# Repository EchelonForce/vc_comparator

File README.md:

# Eurorack Comparator Module

This is a design for a eurorack comparator module using an LM393.

Full writeup here: https://www.robotdialogs.com/2023/01/eurorack-comparator-module.html

This work is licensed under a Creative Commons Attribution-NonCommercial-ShareAlike 4.0 International License. https://creativecommons.org/licenses/by-nc-sa/4.0/

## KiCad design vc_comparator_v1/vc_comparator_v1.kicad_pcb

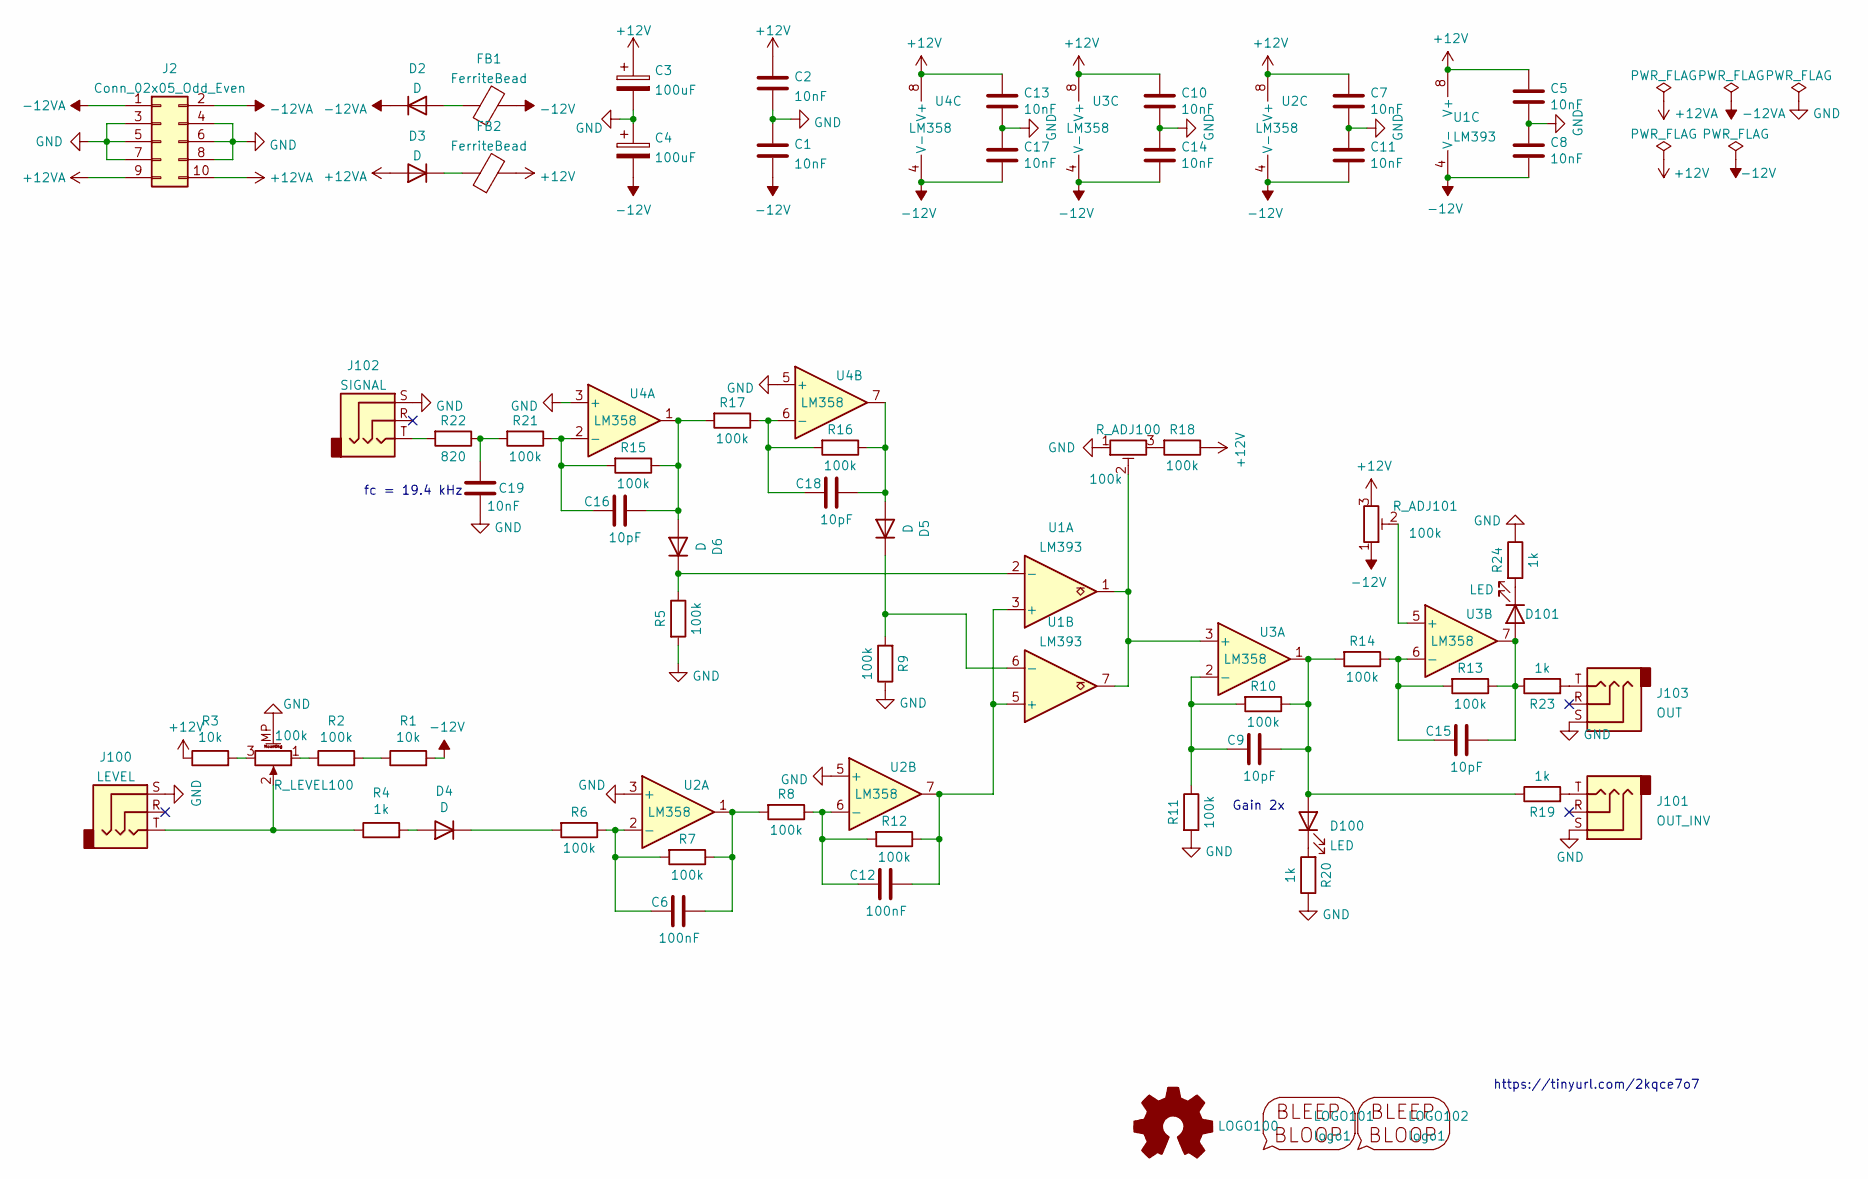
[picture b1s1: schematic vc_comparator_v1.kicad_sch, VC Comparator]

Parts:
C1, C2, C5, C7, C8, C10, C11, C13, C14, C17, C19: 10nF; C_1206_3216Metric_Pad1.33x1.80mm_HandSolder
C3, C4: 100uF; CP_Radial_D5.0mm_P2.50mm
C6, C12: 100nF; C_1206_3216Metric_Pad1.33x1.80mm_HandSolder
C9, C15, C16, C18: 10pF; C_1206_3216Metric_Pad1.33x1.80mm_HandSolder
D2, D3, D4, D5, D6: D; D_A-405_P2.54mm_Vertical_KathodeUp
D100, D101: LED; LED_D3.0mm
FB1, FB2: FerriteBead; L_Axial_L6.6mm_D2.7mm_P2.54mm_Vertical_Vishay_IM-2
J2: Conn_02x05_Odd_Even; IDC-Header_2x05_P2.54mm_Vertical
J100: LEVEL; Jack_3.5mm_MJ-355W_Vertical
J101: OUT_INV; Jack_3.5mm_MJ-355W_Vertical
J102: SIGNAL; Jack_3.5mm_MJ-355W_Vertical
J103: OUT; Jack_3.5mm_MJ-355W_Vertical
LOGO100: Logo_Open_Hardware_Small; OSHW-Symbol_6.7x6mm_SilkScreen
LOGO101: logo1; Logo1
LOGO102: logo1; Logo2
R1, R3: 10k; R_1206_3216Metric_Pad1.30x1.75mm_HandSolder
R2, R5, R6, R7, R8, R9, R10, R11, R12, R13, R14, R15, R16, R17, R18, R21: 100k; R_1206_3216Metric_Pad1.30x1.75mm_HandSolder
R4, R19, R20, R23, R24: 1k; R_1206_3216Metric_Pad1.30x1.75mm_HandSolder
R22: 820; R_1206_3216Metric_Pad1.30x1.75mm_HandSolder
R_ADJ100, R_ADJ101: 100k; Potentiometer_Bourns_3296W_Vertical
R_LEVEL100: 100k; Potentiometer_Alpha_RD901F-40-00D_Single_Vertical_w_3d
U1: LM393; DIP-8_W7.62mm_Socket_LongPads
U2, U3, U4: LM358; DIP-8_W7.62mm_Socket_LongPads

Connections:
+12V: C2.1, C3.1, C5.2, C7.2, C10.2, C13.2, FB2.2, R3.1, R18.1, R_ADJ101.3, U1.8 (V+), U2.8 (V+), U3.8 (V+), U4.8 (V+)
+12VA: D3.2 (A), J2.9, J2.10
-12V: C1.2, C4.2, C8.1, C11.1, C14.1, C17.1, FB1.2, R1.2, R_ADJ101.1, U1.4 (V-), U2.4 (V-), U3.4 (V-), U4.4 (V-)
-12VA: D2.1 (K), J2.1, J2.2
GND: C1.1, C2.2, C3.2, C4.1, C5.1, C7.1, C8.2, C10.1, C11.2, C13.1, C14.2, C17.2, C19.2, J2.3, J2.4, J2.5, J2.6, J2.7, J2.8, J100.S, J101.S, J102.S, J103.S, R5.2, R9.1, R11.2, R20.1, R24.1, R_ADJ100.1, R_LEVEL100.MP (MountPin), U2.3 (+), U2.5 (+), U4.3 (+), U4.5 (+)
unnamed: C6.1, R7.1, R8.2, U2.1
unnamed: C6.2, R6.1, R7.2, U2.2 (-)
unnamed: C9.1, D100.2 (A), R10.1, R14.2, R19.1, U3.1
unnamed: C9.2, R10.2, R11.1, U3.2 (-)
unnamed: C12.1, R12.1, U1.3 (+), U1.5 (+), U2.7
unnamed: C12.2, R8.1, R12.2, U2.6 (-)
unnamed: C15.1, D101.2 (A), R13.1, R23.1, U3.7
unnamed: C15.2, R13.2, R14.1, U3.6 (-)
unnamed: C16.1, D6.2 (A), R15.1, R17.2, U4.1
unnamed: C16.2, R15.2, R21.1, U4.2 (-)
unnamed: C18.1, D5.2 (A), R16.1, U4.7
unnamed: C18.2, R16.2, R17.1, U4.6 (-)
unnamed: C19.1, R21.2, R22.1
unnamed: D2.2 (A), FB1.1
unnamed: D3.1 (K), FB2.1
unnamed: D4.1 (K), R6.2
unnamed: D4.2 (A), R4.2
unnamed: D5.1 (K), R9.2, U1.6 (-)
unnamed: D6.1 (K), R5.1, U1.2 (-)
unnamed: D100.1 (K), R20.2
unnamed: D101.1 (K), R24.2
unnamed: J100.T, R4.1, R_LEVEL100.2
unnamed: J101.T, R19.2
unnamed: J102.T, R22.2
unnamed: J103.T, R23.2
unnamed: R2.1, R_LEVEL100.1
unnamed: R1.1, R2.2
unnamed: R3.2, R_LEVEL100.3
unnamed: R18.2, R_ADJ100.3
unnamed: R_ADJ100.2, U1.1, U1.7, U3.3 (+)
unnamed: R_ADJ101.2, U3.5 (+)

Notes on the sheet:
fc = 19.4 kHz
Gain 2x
https://tinyurl.com/2kqce7o7

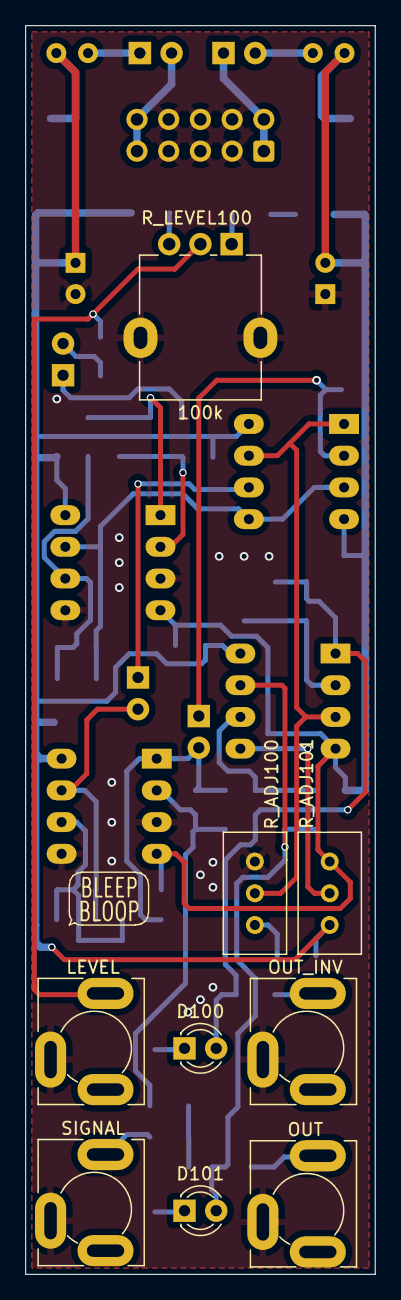
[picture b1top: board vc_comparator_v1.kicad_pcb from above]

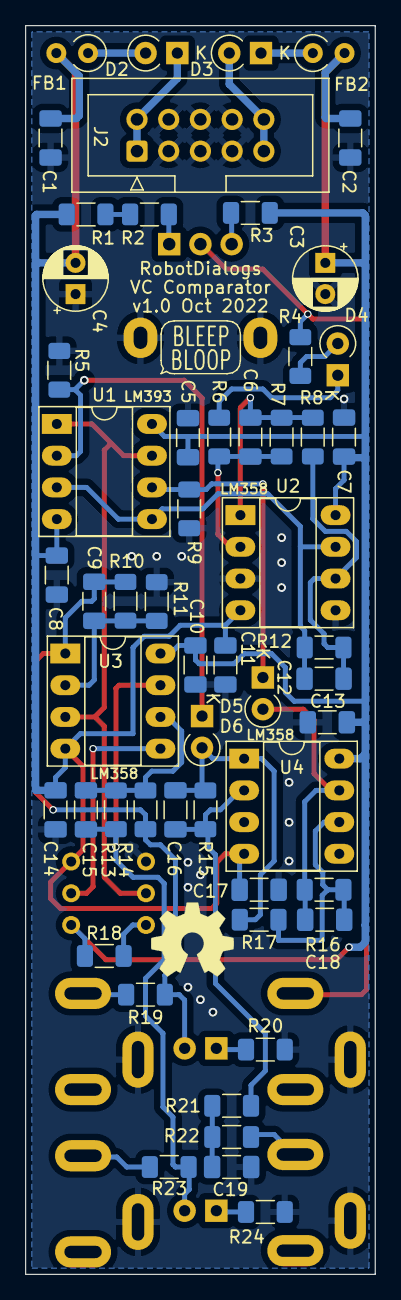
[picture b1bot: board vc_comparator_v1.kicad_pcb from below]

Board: 2 copper layers, 28.0 x 100.0 mm, 67 parts (56 on the bottom side), 36 nets.

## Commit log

2022-10-09 Initial commit with .gitignore
2022-10-09 Schematic and layout draft
2022-10-15 Geographic re-annotate and cleanup
2022-10-15 Panelized v1
2022-10-24 Front Panel v1 CAD
2022-10-24 Notes update
2023-01-18 Redlined v1 schematic and updates.
2023-01-18 Add README
